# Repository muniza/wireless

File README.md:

# Wireless Club Experiments

This repo houses the experiments that I created for the wireless club in an effort to increase student interest in wireless radio and hacking
* fm_tx is a 1" by 1" wireless bug made in Eagle

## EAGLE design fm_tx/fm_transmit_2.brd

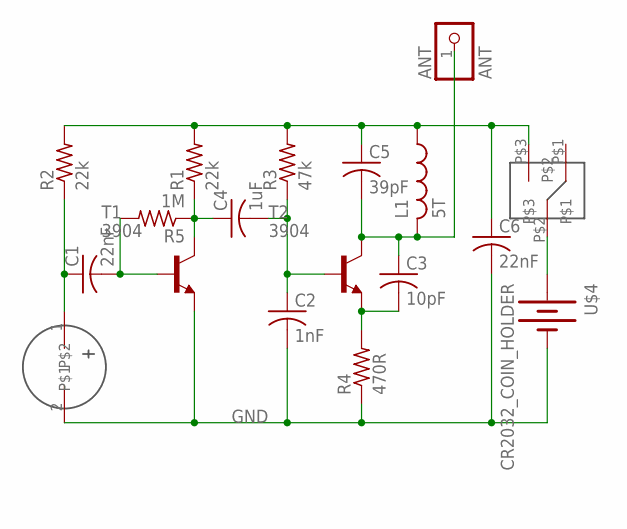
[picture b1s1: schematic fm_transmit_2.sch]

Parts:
ANT: ANT; 1X01
C1, C6: 22nF; C1206
C2: 1nF; C1206
C3: 10pF; C1206
C4: 1uF; C1206
C5: 39pF; C1206
L1: 5T; 0207/15
R1, R2: 22k; R1206
R3: 47k; R1206
R4: 470R; R1206
R5: 1M; R1206
T1, T2: 3904; SOT23-BEC
U$1: SPDT; SWITCH
U$2: MIC
U$4: CR2032_COIN_HOLDER; COIN_HOLDER

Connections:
+3V: U$1.P$2, U$4.P$1 (+), U$4.P$2 (+), U$4.P$3 (+), U$4.P$4 (+)
GND: C2.2, C6.2, R4.1, T1.E, U$2.2, U$4.P$5 (-)
unnamed: C1.2, R5.2, T1.B
unnamed: C4.1, R1.1, R5.1, T1.C
unnamed: C1.1, R2.1, U$2.1
unnamed: C2.1, C4.2, R3.1, T2.B
unnamed: ANT.1, C3.1, C5.2, L1.2, T2.C
unnamed: C5.1, C6.1, L1.1, R1.2, R2.2, R3.2, U$1.P$3
unnamed: C3.2, R4.2, T2.E

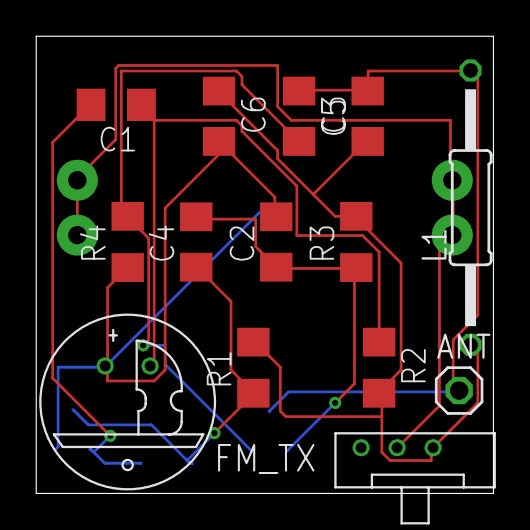
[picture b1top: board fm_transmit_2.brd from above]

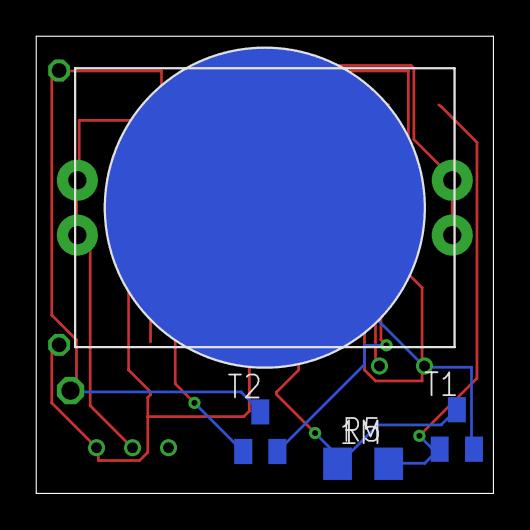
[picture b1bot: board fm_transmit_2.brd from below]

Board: 2 copper layers, 25.4 x 25.4 mm, 18 parts (4 on the bottom side), 9 nets.

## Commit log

2015-01-16 added files for fm transmitter
